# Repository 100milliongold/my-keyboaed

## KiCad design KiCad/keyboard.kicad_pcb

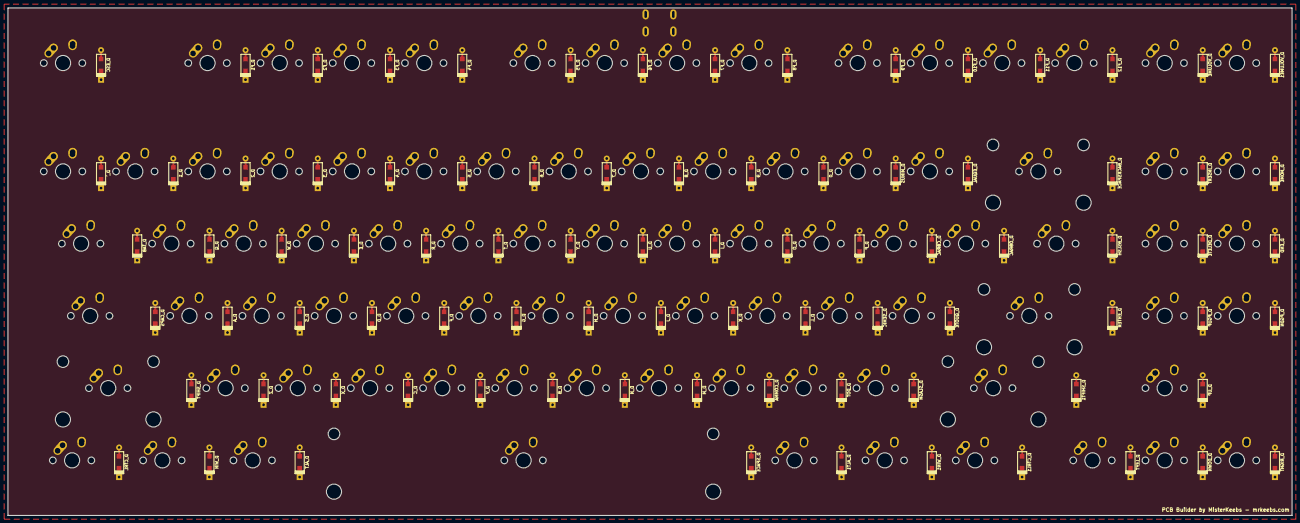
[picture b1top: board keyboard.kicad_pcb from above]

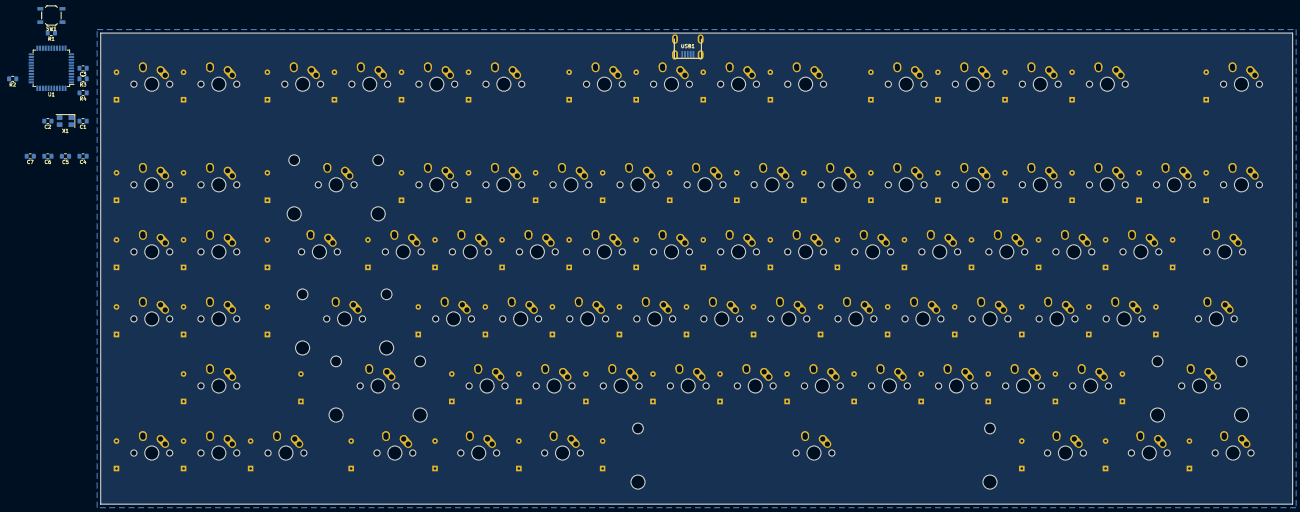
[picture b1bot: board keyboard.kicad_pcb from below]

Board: 2 copper layers, 338.6 x 133.8 mm, 185 parts (15 on the bottom side), 119 nets, no tracks yet.

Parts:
C1, C2, C3, C4, C5, C6, C7: 22pF; C_0805_2012Metric_Pad1.15x1.40mm_HandSolder
D_0, D_1, D_2, D_3, D_4, D_5, D_6, D_7, D_8, D_9: D; D_SOD123_axial
D_A: D; D_SOD123_axial
D_ALT, D_ALT1: D; D_SOD123_axial
D_B: D; D_SOD123_axial
D_BACKSPACE: D; D_SOD123_axial
D_BSLSH: D; D_SOD123_axial
D_C: D; D_SOD123_axial
D_CAPS: D; D_SOD123_axial
D_CBRAC: D; D_SOD123_axial
D_COMMA: D; D_SOD123_axial
D_CTRL, D_CTRL1: D; D_SOD123_axial
D_D: D; D_SOD123_axial
D_DELETE: D; D_SOD123_axial
D_DOT: D; D_SOD123_axial
D_DOWN: D; D_SOD123_axial
D_E: D; D_SOD123_axial
D_END: D; D_SOD123_axial
D_ENTER: D; D_SOD123_axial
D_EQUAL: D; D_SOD123_axial
D_ESC: D; D_SOD123_axial
D_F, D_F1, D_F2, D_F3, D_F4, D_F5, D_F6, D_F7, D_F8, D_F9, D_F10, D_F11, D_F12: D; D_SOD123_axial
D_G: D; D_SOD123_axial
D_H: D; D_SOD123_axial
D_HOME: D; D_SOD123_axial
D_I: D; D_SOD123_axial
D_INSERT: D; D_SOD123_axial
D_J: D; D_SOD123_axial
D_K: D; D_SOD123_axial
D_L: D; D_SOD123_axial
D_LEFT: D; D_SOD123_axial
D_M: D; D_SOD123_axial
D_MINUS: D; D_SOD123_axial
D_N: D; D_SOD123_axial
D_O: D; D_SOD123_axial
D_OBRAC: D; D_SOD123_axial
D_P: D; D_SOD123_axial
D_PGDN: D; D_SOD123_axial
D_PGUP: D; D_SOD123_axial
D_Q: D; D_SOD123_axial
D_QUOTE: D; D_SOD123_axial
D_R: D; D_SOD123_axial
D_RIGHT: D; D_SOD123_axial
D_S: D; D_SOD123_axial
D_SEMIC: D; D_SOD123_axial
D_SHIFT, D_SHIFT1: D; D_SOD123_axial
D_SLASH: D; D_SOD123_axial
D_SPACE: D; D_SOD123_axial
D_T: D; D_SOD123_axial
D_TAB: D; D_SOD123_axial
D_U: D; D_SOD123_axial
D_UP: D; D_SOD123_axial
D_V: D; D_SOD123_axial
D_VOLUME, D_VOLUME1: D; D_SOD123_axial
D_W: D; D_SOD123_axial
D_WIN, D_WIN1: D; D_SOD123_axial
D_X: D; D_SOD123_axial
D_Y: D; D_SOD123_axial
D_Z: D; D_SOD123_axial
D_`: D; D_SOD123_axial
K_0, K_1, K_2, K_3, K_4, K_5, K_6, K_7, K_8, K_9: KEYSW; MX-1U-NoLED
K_A: KEYSW; MX-1U-NoLED
K_ALT, K_ALT1: KEYSW; MX-1.25U-NoLED
K_B: KEYSW; MX-1U-NoLED
K_BACKSPACE: KEYSW; MX-2U-NoLED
K_BSLSH: KEYSW; MX-1.5U-NoLED
K_C: KEYSW; MX-1U-NoLED
K_CAPS: KEYSW; MX-1.75U-NoLED
K_CBRAC: KEYSW; MX-1U-NoLED
K_COMMA: KEYSW; MX-1U-NoLED
K_CTRL, K_CTRL1: KEYSW; MX-1.25U-NoLED
K_D: KEYSW; MX-1U-NoLED
K_DELETE: KEYSW; MX-1U-NoLED
K_DOT: KEYSW; MX-1U-NoLED
K_DOWN: KEYSW; MX-1U-NoLED
K_E: KEYSW; MX-1U-NoLED
K_END: KEYSW; MX-1U-NoLED
K_ENTER: KEYSW; MX-2.25U-NoLED
K_EQUAL: KEYSW; MX-1U-NoLED
K_ESC: KEYSW; MX-1U-NoLED
K_F, K_F1, K_F2, K_F3, K_F4, K_F5, K_F6, K_F7, K_F8, K_F9, K_F10, K_F11, K_F12: KEYSW; MX-1U-NoLED
K_G: KEYSW; MX-1U-NoLED
K_H: KEYSW; MX-1U-NoLED
K_HOME: KEYSW; MX-1U-NoLED
K_I: KEYSW; MX-1U-NoLED
K_INSERT: KEYSW; MX-1U-NoLED
K_J: KEYSW; MX-1U-NoLED
K_K: KEYSW; MX-1U-NoLED
K_L: KEYSW; MX-1U-NoLED
K_LEFT: KEYSW; MX-1U-NoLED
K_M: KEYSW; MX-1U-NoLED
K_MINUS: KEYSW; MX-1U-NoLED
K_N: KEYSW; MX-1U-NoLED
K_O: KEYSW; MX-1U-NoLED
K_OBRAC: KEYSW; MX-1U-NoLED
K_P: KEYSW; MX-1U-NoLED
K_PGDN: KEYSW; MX-1U-NoLED
K_PGUP: KEYSW; MX-1U-NoLED
K_Q: KEYSW; MX-1U-NoLED
K_QUOTE: KEYSW; MX-1U-NoLED
K_R: KEYSW; MX-1U-NoLED
K_RIGHT: KEYSW; MX-1U-NoLED
K_S: KEYSW; MX-1U-NoLED
K_SEMIC: KEYSW; MX-1U-NoLED
K_SHIFT, K_SHIFT1: KEYSW; MX-2.25U-NoLED
K_SLASH: KEYSW; MX-1U-NoLED
K_SPACE: KEYSW; MX-6.25U-NoLED
K_T: KEYSW; MX-1U-NoLED
K_TAB: KEYSW; MX-1.5U-NoLED
K_U: KEYSW; MX-1U-NoLED
K_UP: KEYSW; MX-1U-NoLED
K_V: KEYSW; MX-1U-NoLED
K_VOLUME, K_VOLUME1: KEYSW; MX-1U-NoLED
K_W: KEYSW; MX-1U-NoLED
K_WIN, K_WIN1: KEYSW; MX-1.25U-NoLED
K_X: KEYSW; MX-1U-NoLED
K_Y: KEYSW; MX-1U-NoLED
K_Z: KEYSW; MX-1U-NoLED
K_`: KEYSW; MX-1U-NoLED
R1, R2: 10k; R_0805_2012Metric_Pad1.15x1.40mm_HandSolder
R3, R4: 22; R_0805_2012Metric_Pad1.15x1.40mm_HandSolder
SW1: SW_PUSH; SW_SPST_TL3342
U1: ATMEGA32U4; TQFP-44_10x10mm_P0.8mm
USB1: Molex-0548190589; Molex-0548190589-Assembly
X1: XTAL_GND; Crystal_SMD_5032-4Pin_5.0x3.2mm

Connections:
/col0: K_CAPS.1, K_CTRL.1, K_ESC.1, K_TAB.1, K_`.1, U1.41
/col1: K_1.1, K_SHIFT.1, K_WIN.1, U1.40
/col2: K_2.1, K_A.1, K_F1.1, K_Q.1, K_Z.1, U1.39
/col3: K_3.1, K_ALT.1, K_F2.1, K_S.1, K_W.1, K_X.1, U1.38
/col4: K_4.1, K_C.1, K_D.1, K_E.1, K_F3.1, U1.37
/col5: K_5.1, K_F.1, K_F4.1, K_R.1, K_V.1, U1.36
/col6: K_6.1, K_B.1, K_G.1, K_SPACE.1, K_T.1, U1.32
/col7: K_7.1, K_F5.1, K_H.1, K_N.1, K_Y.1, U1.31
/col8: K_8.1, K_F6.1, K_J.1, K_M.1, K_U.1, U1.30
/col9: K_9.1, K_COMMA.1, K_F7.1, K_I.1, K_K.1, U1.29
/col10: K_0.1, K_ALT1.1, K_DOT.1, K_F8.1, K_L.1, K_O.1, U1.28
/col11: K_F9.1, K_MINUS.1, K_P.1, K_SEMIC.1, K_SLASH.1, K_WIN1.1, U1.27
/col12: K_CBRAC.1, K_EQUAL.1, K_F10.1, K_QUOTE.1, U1.26
/col13: K_CTRL1.1, K_ENTER.1, K_F11.1, K_OBRAC.1, K_SHIFT1.1, U1.25
/col14: K_BACKSPACE.1, K_BSLSH.1, K_F12.1, K_LEFT.1, U1.22
/col15: K_DELETE.1, K_DOWN.1, K_INSERT.1, K_PGUP.1, K_UP.1, K_VOLUME.1, U1.21
/col16: K_END.1, K_HOME.1, K_PGDN.1, K_RIGHT.1, K_VOLUME1.1, U1.20
/row0: D_ESC.1, D_F1.1, D_F2.1, D_F3.1, D_F4.1, D_F5.1, D_F6.1, D_F7.1, D_F8.1, D_F9.1, D_F10.1, D_F11.1, D_F12.1, D_VOLUME.1, D_VOLUME1.1, U1.8
/row2: D_0.1, D_1.1, D_2.1, D_3.1, D_4.1, D_5.1, D_6.1, D_7.1, D_8.1, D_9.1, D_BACKSPACE.1, D_EQUAL.1, D_HOME.1, D_INSERT.1, D_MINUS.1, D_`.1, U1.10
/row3: D_BSLSH.1, D_CBRAC.1, D_DELETE.1, D_E.1, D_END.1, D_I.1, D_O.1, D_OBRAC.1, D_P.1, D_Q.1, D_R.1, D_T.1, D_TAB.1, D_U.1, D_W.1, D_Y.1, U1.11
/row4: D_A.1, D_CAPS.1, D_D.1, D_ENTER.1, D_F.1, D_G.1, D_H.1, D_J.1, D_K.1, D_L.1, D_PGDN.1, D_PGUP.1, D_QUOTE.1, D_S.1, D_SEMIC.1, U1.12
/row5: D_B.1, D_C.1, D_COMMA.1, D_DOT.1, D_M.1, D_N.1, D_SHIFT.1, D_SHIFT1.1, D_SLASH.1, D_UP.1, D_V.1, D_X.1, D_Z.1, U1.18
/row6: D_ALT.1, D_ALT1.1, D_CTRL.1, D_CTRL1.1, D_DOWN.1, D_LEFT.1, D_RIGHT.1, D_SPACE.1, D_WIN.1, D_WIN1.1, U1.19
GND: C1.2, C2.2, C3.2, C4.2, C5.2, C6.2, C7.2, R2.2, SW1.1, U1.5, U1.15, U1.23, USB1.1, X1.2, X1.4
unnamed: C1.1, U1.16, X1.1
unnamed: C2.1, U1.17, X1.3
unnamed: C3.1, U1.6
unnamed: D_0.2, K_0.2
unnamed: D_1.2, K_1.2
unnamed: D_2.2, K_2.2
unnamed: D_3.2, K_3.2
unnamed: D_4.2, K_4.2
unnamed: D_5.2, K_5.2
unnamed: D_6.2, K_6.2
unnamed: D_7.2, K_7.2
unnamed: D_8.2, K_8.2
unnamed: D_9.2, K_9.2
unnamed: D_A.2, K_A.2
unnamed: D_ALT1.2, K_ALT1.2
unnamed: D_ALT.2, K_ALT.2
unnamed: D_B.2, K_B.2
unnamed: D_BACKSPACE.2, K_BACKSPACE.2
unnamed: D_BSLSH.2, K_BSLSH.2
unnamed: D_C.2, K_C.2
unnamed: D_CAPS.2, K_CAPS.2
unnamed: D_CBRAC.2, K_CBRAC.2
unnamed: D_COMMA.2, K_COMMA.2
unnamed: D_CTRL1.2, K_CTRL1.2
unnamed: D_CTRL.2, K_CTRL.2
unnamed: D_D.2, K_D.2
unnamed: D_DELETE.2, K_DELETE.2
unnamed: D_DOT.2, K_DOT.2
unnamed: D_DOWN.2, K_DOWN.2
unnamed: D_E.2, K_E.2
unnamed: D_END.2, K_END.2
unnamed: D_ENTER.2, K_ENTER.2
unnamed: D_EQUAL.2, K_EQUAL.2
unnamed: D_ESC.2, K_ESC.2
unnamed: D_F1.2, K_F1.2
unnamed: D_F2.2, K_F2.2
unnamed: D_F3.2, K_F3.2
unnamed: D_F4.2, K_F4.2
unnamed: D_F5.2, K_F5.2
unnamed: D_F6.2, K_F6.2
unnamed: D_F7.2, K_F7.2
unnamed: D_F8.2, K_F8.2
unnamed: D_F9.2, K_F9.2
unnamed: D_F10.2, K_F10.2
unnamed: D_F11.2, K_F11.2
unnamed: D_F12.2, K_F12.2
unnamed: D_F.2, K_F.2
unnamed: D_G.2, K_G.2
unnamed: D_H.2, K_H.2
unnamed: D_HOME.2, K_HOME.2
unnamed: D_I.2, K_I.2
unnamed: D_INSERT.2, K_INSERT.2
unnamed: D_J.2, K_J.2
unnamed: D_K.2, K_K.2
unnamed: D_L.2, K_L.2
unnamed: D_LEFT.2, K_LEFT.2
unnamed: D_M.2, K_M.2
unnamed: D_MINUS.2, K_MINUS.2
unnamed: D_N.2, K_N.2
unnamed: D_O.2, K_O.2
unnamed: D_OBRAC.2, K_OBRAC.2
unnamed: D_P.2, K_P.2
unnamed: D_PGDN.2, K_PGDN.2
unnamed: D_PGUP.2, K_PGUP.2
unnamed: D_Q.2, K_Q.2
unnamed: D_QUOTE.2, K_QUOTE.2
unnamed: D_R.2, K_R.2
unnamed: D_RIGHT.2, K_RIGHT.2
unnamed: D_S.2, K_S.2
unnamed: D_SEMIC.2, K_SEMIC.2
unnamed: D_SHIFT1.2, K_SHIFT1.2
unnamed: D_SHIFT.2, K_SHIFT.2
unnamed: D_SLASH.2, K_SLASH.2
unnamed: D_SPACE.2, K_SPACE.2
unnamed: D_T.2, K_T.2
unnamed: D_TAB.2, K_TAB.2
unnamed: D_U.2, K_U.2
unnamed: D_UP.2, K_UP.2
unnamed: D_V.2, K_V.2
unnamed: D_VOLUME1.2, K_VOLUME1.2
unnamed: D_VOLUME.2, K_VOLUME.2
unnamed: D_W.2, K_W.2
unnamed: D_WIN1.2, K_WIN1.2
unnamed: D_WIN.2, K_WIN.2
unnamed: D_X.2, K_X.2
unnamed: D_Y.2, K_Y.2
unnamed: D_Z.2, K_Z.2
unnamed: D_`.2, K_`.2
unnamed: R1.1, SW1.2, U1.13
unnamed: R2.1, U1.33
unnamed: R3.1, U1.3
unnamed: R4.1, U1.4
unnamed: R3.2, USB1.2
unnamed: R4.2, USB1.3
VCC: C4.1, C5.1, C6.1, C7.1, R1.2, U1.2, U1.14, U1.24, USB1.5

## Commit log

2022-09-15 키보드 변경
2022-09-15 배선 변경
2022-09-15 기판 완성
2022-09-15 거버 파일 및 BOM 리스트 추가
2022-09-16 불필요한 이모티콘 제거
